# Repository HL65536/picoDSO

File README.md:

# picoDSO
================

**Open-Source Oscilloscope based on the Raspberry Pi Pico**

## Project Status
---------------

The minimum viable product is ready, and development of new features is 
ongoing. Updates will be published regularly, although the pace may be 
slow.

## Key Features
--------------

* **Flexible Data Acquisition**: Use either the internal ADC(s) of the 
Raspberry Pi Pico to measure up to ~2MSa/s or 1-2 faster external ADCs 
(requires a custom PCB) for >50MSa/s at 8 bit.
* **Optional PCB**: The project can be built on a breadboard or with an 
optional PCB for easier assembly and improved performance.
* **Display Options**: Supports both SSD1306 and ST7789 displays, with 
potential support for more in the future.

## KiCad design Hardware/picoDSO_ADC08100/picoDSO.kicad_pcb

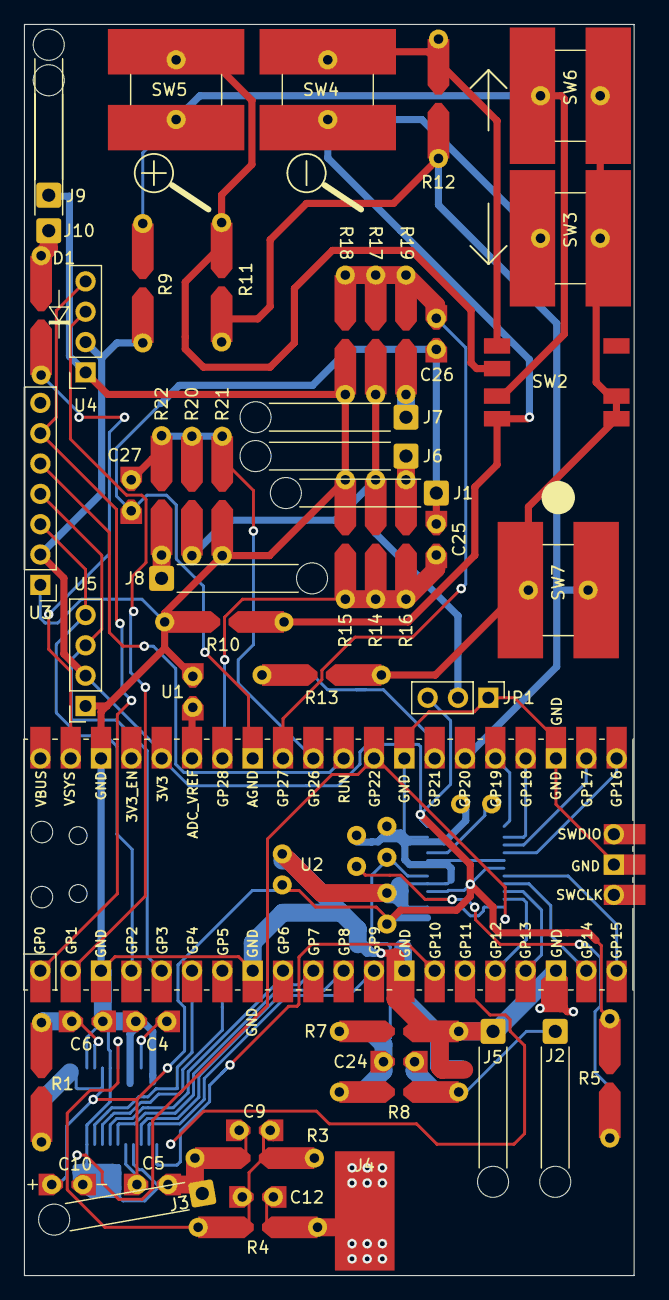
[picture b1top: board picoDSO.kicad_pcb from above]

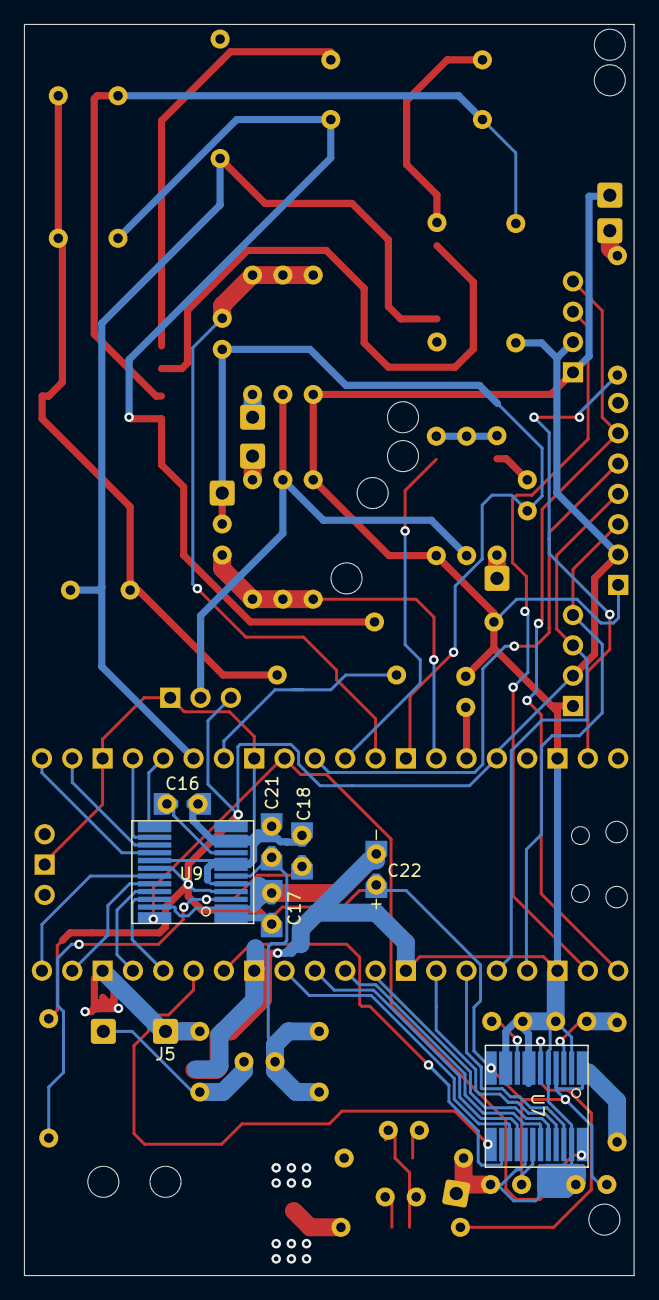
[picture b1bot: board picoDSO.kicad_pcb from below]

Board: 2 copper layers, 51.1 x 104.8 mm, 60 parts (7 on the bottom side), 50 nets.

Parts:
C4, C5, C6, C16, C17, C18: 100nF; universalMixed
C9, C21: Cdiv_bot; universalMixed
C10, C22: C_Polarized; universalMixedElectrolyticCap
C12, C24: Cdiv_top; universalMixed
C25, C26, C27: 68pF; universalMixed
D1: D_Schottky; universalMixedDiode
J1: internalADC_GND; SolderWire-0.5sqmm_1x01_D0.9mm_OD2.1mm_Relief
J2: chip1_probe+; SolderWire-0.5sqmm_1x01_D0.9mm_OD2.1mm_Relief
J3, J5: probeGND; SolderWire-0.5sqmm_1x01_D0.9mm_OD2.1mm_Relief
J4: chip0_probe+; SolderWirePad_1x01_SMD_5x10mm
J6, J7, J8: probeConnector; SolderWire-0.5sqmm_1x01_D0.9mm_OD2.1mm_Relief
J9: bat_GND; SolderWire-0.5sqmm_1x01_D0.9mm_OD2.1mm_Relief
J10: bat+; SolderWire-0.5sqmm_1x01_D0.9mm_OD2.1mm_Relief
JP1: internalADC_rangeselJumper; PinHeader_1x03_P2.54mm_Vertical
R1, R5: R; universalMixedLong
R3, R7: Rdiv_bot; universalMixedLong
R4, R8: Rdiv_top; universalMixedLong
R9, R10: 470; universalMixedLong
R11, R12: 4.7k; universalMixedLong
R13: 1k; universalMixedLong
R14, R15, R17, R18, R20, R21: 22k; universalMixedLong
R16, R19, R22: 100k; universalMixedLong
SW2: JoystickSwitch
SW3: dir2_alt; universalButton
SW4: dir4_alt; universalButton
SW5: dir3_alt; universalButton
SW6: dir1_alt; universalButton
SW7: button; universalButton
U1: optional_externalVREF; universalMixed
U2: Pico; RPi_Pico_SMD_TH
U3: ST7789; PinHeader_1x07_P2.54mm_Vertical
U4: SSD1306_Display1; PinSocket_1x04_P2.54mm_Vertical
U5: SSD1306_Display2; PinSocket_1x04_P2.54mm_Vertical
U7, U9: ADC08060; TSSOP-24 hand solder

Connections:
+3V3: C5.1, C10.1, C17.1, C22.1, JP1.3 (B), R1.2, R5.2, R9.1, U2.36 (3V3), U3.2 (VCC), U4.2 (VCC), U5.2 (VCC), U7.1 (AVDD), U7.4 (AVDD), U7.12 (AVDD), U7.18 (DVDD), U9.1 (AVDD), U9.4 (AVDD), U9.12 (AVDD), U9.18 (DVDD)
+BATT: D1.2 (A), J10.1
/ADC_chip0/clk: U2.29 (GPIO22), U7.24 (CLK), U9.24 (CLK)
/ADC_chip0/p0: U2.6 (GPIO4), U7.22 (D7)
/ADC_chip0/p1: U2.7 (GPIO5), U7.21 (D6)
/ADC_chip0/p2: U2.9 (GPIO6), U7.20 (D5)
/ADC_chip0/p3: U2.10 (GPIO7), U7.19 (D4)
/ADC_chip0/p4: U2.11 (GPIO8), U7.16 (D3)
/ADC_chip0/p5: U2.12 (GPIO9), U7.15 (D2)
/ADC_chip0/p6: U2.14 (GPIO10), U7.14 (D1)
/ADC_chip0/p7: U2.15 (GPIO11), U7.13 (D0)
/ADC_chip0/probe+: C12.1, J4.1, R4.1
/ADC_chip1/p0: U2.16 (GPIO12), U9.22 (D7)
/ADC_chip1/p1: U2.17 (GPIO13), U9.21 (D6)
/ADC_chip1/p2: U2.19 (GPIO14), U9.20 (D5)
/ADC_chip1/p3: U2.20 (GPIO15), U9.19 (D4)
/ADC_chip1/p4: U2.21 (GPIO16), U9.16 (D3)
/ADC_chip1/p5: U2.22 (GPIO17), U9.15 (D2)
/ADC_chip1/p6: U2.24 (GPIO18), U9.14 (D1)
/ADC_chip1/p7: U2.25 (GPIO19), U9.13 (D0)
/ADC_chip1/probe+: C24.1, J2.1, R8.1
/internalADCinput0/ADCpin: C27.1, R20.2, R21.1, R22.2, U2.31 (GPIO26_ADC0)
/internalADCinput1/ADCpin: C26.1, R17.2, R18.1, R19.2, U2.32 (GPIO27_ADC1)
/internalADCinput2/ADCpin: C25.1, R14.2, R15.1, R16.2, U2.34 (GPIO28_ADC2)
/navButtons/pin1: R13.1, U2.27 (GPIO21)
/navButtons/pin2: R11.2, R12.1, SW7.2, U2.26 (GPIO20)
GND: C4.2, C5.2, C6.2, C9.2, C10.2, C16.2, C17.2, C18.2, C21.2, C22.2, J3.1, J5.1, J9.1, JP1.1 (A), R3.2, R7.2, R10.2, R15.2, R18.2, R21.2, U1.2 (A), U2.3 (GND), U2.8 (GND), U2.13 (GND), U2.18 (GND), U2.23 (GND), U2.28 (GND), U2.38 (GND), U2.42 (GND), U3.1 (GND), U4.1 (GND), U5.1 (GND), U7.2 (AGND), U7.5 (AGND), U7.7 (VIN_GND), U7.8 (DGND), U7.10 (VRB), U7.11 (AGND), U7.17 (DGND), U7.23 (PWR_DWN), U9.2 (AGND), U9.5 (AGND), U9.7 (VIN_GND), U9.8 (DGND), U9.10 (VRB), U9.11 (AGND), U9.17 (DGND), U9.23 (PWR_DWN)
GNDA: C25.2, C26.2, C27.2, J1.1, U2.33 (AGND)
unnamed: C4.1, U7.9 (VRB)
unnamed: C6.1, R1.1, U7.3 (VRT)
unnamed: C9.1, C12.2, R3.1, R4.2, U7.6 (AIN)
unnamed: C16.1, U9.9 (VRB)
unnamed: C18.1, R5.1, U9.3 (VRT)
unnamed: C21.1, C24.2, R7.1, R8.2, U9.6 (AIN)
unnamed: D1.1 (K), U2.39 (VSYS)
unnamed: J6.1, R16.1
unnamed: J7.1, R19.1
unnamed: J8.1, R22.1
unnamed: R9.2, SW2.3 (1&3), SW5.1, SW6.1
unnamed: R10.1, SW2.4 (2&4), SW3.1, SW4.1
unnamed: R11.1, SW2.2 (dir3), SW5.2
unnamed: R12.2, SW2.1 (dir4), SW4.2
unnamed: R13.2, SW2.5 (dir2), SW2.6 (dir1), SW3.2, SW6.2, SW7.1
unnamed: U1.1 (K), U2.35 (ADC_VREF)
unnamed: U2.1 (GPIO0), U3.6 (DC), U4.4 (SDA)
unnamed: U2.2 (GPIO1), U4.3 (SCL)
unnamed: U2.4 (GPIO2), U3.3 (CLK), U5.4 (SDA)
unnamed: U2.5 (GPIO3), U3.4 (DAT), U5.3 (SCL)
unnamed: U2.30 (RUN), U3.5 (RES)
internalADCrangeSel: JP1.2 (C), R14.1, R17.1, R20.1

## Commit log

2024-09-16 Added KiCad files
    KiCad files for ADC08100 family and ADS830E family chips. Generic board with multiple parts options.
2025-06-17 added v0.1.0 of oscilloscope firmware
    It should have been there along with the initial hardware version (oops). Uses a fixed configuration for single external ADC chip (default 60MHz).
2025-06-17 Fixed voltage scale, refactored code
    The displayed voltage scaling for the graph is now correct
    PIO code is now changed to new, cleaner system using wrapper
    Use recording class instead of raw arrays for data acquisition and storage
    Files for future 3-bit framebuffer added
